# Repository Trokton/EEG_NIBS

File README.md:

# EEG_NIBS

🧠 Closed-Loop EEG & 4-Channel tACS/tDCS Neurostimulation System

Welcome to the documentation for a fully open-source, closed-loop EEG-integrated neurostimulation system, built entirely from scratch.

This repository contains the hardware designs, parts list, and firmware for a 4-channel tACS/tDCS stimulation system with real-time EEG integration, controlled via Python and Arduino Nano.

⸻

🧩 Project Overview

This system was developed to explore adaptive brain stimulation — modulating electrical currents based on real-time brain states, cognitive performance, or reinforcement learning algorithms.

Key Components:
	•	🧠 EEG Recording Module
	•	⚡ 4-Channel tDCS/tACS Stimulation Hardware
	•	🔁 Closed-Loop Python Control System
	•	🖥️ Arduino-based DAC current control
	•	🔐 Built-in Safety Features & Logging

The system is designed to serve researchers and developers interested in:
	•	Personalized neurostimulation
	•	Cognitive enhancement
	•	Reinforcement learning in neuroscience
	•	Brain-computer interfaces (BCIs)
	•	DIY neuroscience and open science hardware

⸻

🎯 Purpose

To provide a low-cost, flexible, and safe neurotechnology platform for:
	•	Closed-loop stimulation experiments
	•	Adaptive stimulation based on EEG/behavioral input
	•	Neuroscientific prototyping for brain state modulation
	•	Psychophysiological experiments

⸻

🛠️ Hardware Specifications

🔌 Stimulation Module (4-Channel tDCS/tACS)

Spec	Value/Feature
Channels	4 (individually addressable)
Max Current (per channel)	4 mA
Modulation Modes	tDCS, tACS (Sine, Square, Ramp, Custom)
Control Interface	Arduino Nano + DAC7311
Current Regulation	DAC-controlled + precision resistors
Voltage Reference	REF5050 or ADR5041 (5.0V)
Safety Features	Emergency analog cut-off, max current limit, resistance monitoring
Program Modes	5 fixed presets (2 x tDCS, 3 x tACS)
Control UI	1.3” OLED + 4 Buttons (Program, Start/Stop, ±Current)
Power Supply	Lab power (battery optional)

⸻

🧠 EEG Integration
	•	Interface for real-time EEG signal acquisition (designed for compatibility with OpenBCI or DIY amplifier)
	•	Real-time data streaming to Python
	•	Used to compute state, reward, and adaptation signals
	•	Clean switching logic to avoid interference during stimulation
	•	Log-based and adaptive session management

⸻

🧰 Bill of Materials (BoM)

(Full parts list available in parts_catalog.xlsx)

Example components:
	•	Arduino Nano (x4)
	•	DAC7311IDCKR (x2)
	•	TLC2252 Op-Amps (x4)
	•	REF5050 / ADR5041 Voltage Reference
	•	86.6Ω, 1.2kΩ, 2.2kΩ precision resistors
	•	1µF MLCC capacitors
	•	L78L05 voltage regulator
	•	SI8630BD Digital Isolator
	•	FMMT734/634 Darlington Transistors
	•	OLED 1.3” Display
	•	Tactile Buttons (x4)
	•	Toggle/Emergency Switch
	•	XL6009 Boost Converter

⸻

💻 Software / Firmware
	•	Arduino Sketches: arduino_code/
	•	Python Control Scripts (planned): python_control/
	•	EEG Integration & Analysis: eeg_pipeline/
	•	Safety & Log Scripts: logs/

⸻

🔄 Closed-Loop Flow
	1.	Cognitive Task → EEG + Task Performance Monitoring
	2.	Python Agent → Define State
	3.	RL Algorithm → Select Stimulation Protocol (Action)
	4.	Arduino Executes Program via DAC
	5.	EEG Feedback → Reward + Adaptation

⸻

📷 Visuals

PCB Layout, 3D Case Design, and Build Photos are included in assets/.

⸻

⚠️ Safety Notes
	•	Always monitor electrode resistance.
	•	Do not exceed 4 mA/channel.
	•	Use ramp-up/ramp-down transitions.
	•	Test with resistive dummy loads before skin contact.

⸻

👤 Author

Developed by Michael Roehrig, psychologist & AI enthusiast, diving into DIY neurotech to build accessible and intelligent brain interfaces.

Inspired by the incredible work of Prof. Roi Cohen Kadosh and open science communities.

⸻

📩 Contact & Collaboration

Interested in collaboration, replication, or feedback? Let’s connect via LinkedIn or GitHub issues!

⸻

📜 License

Open-source for research and educational use. Use responsibly. Not intended for clinical/medical use.

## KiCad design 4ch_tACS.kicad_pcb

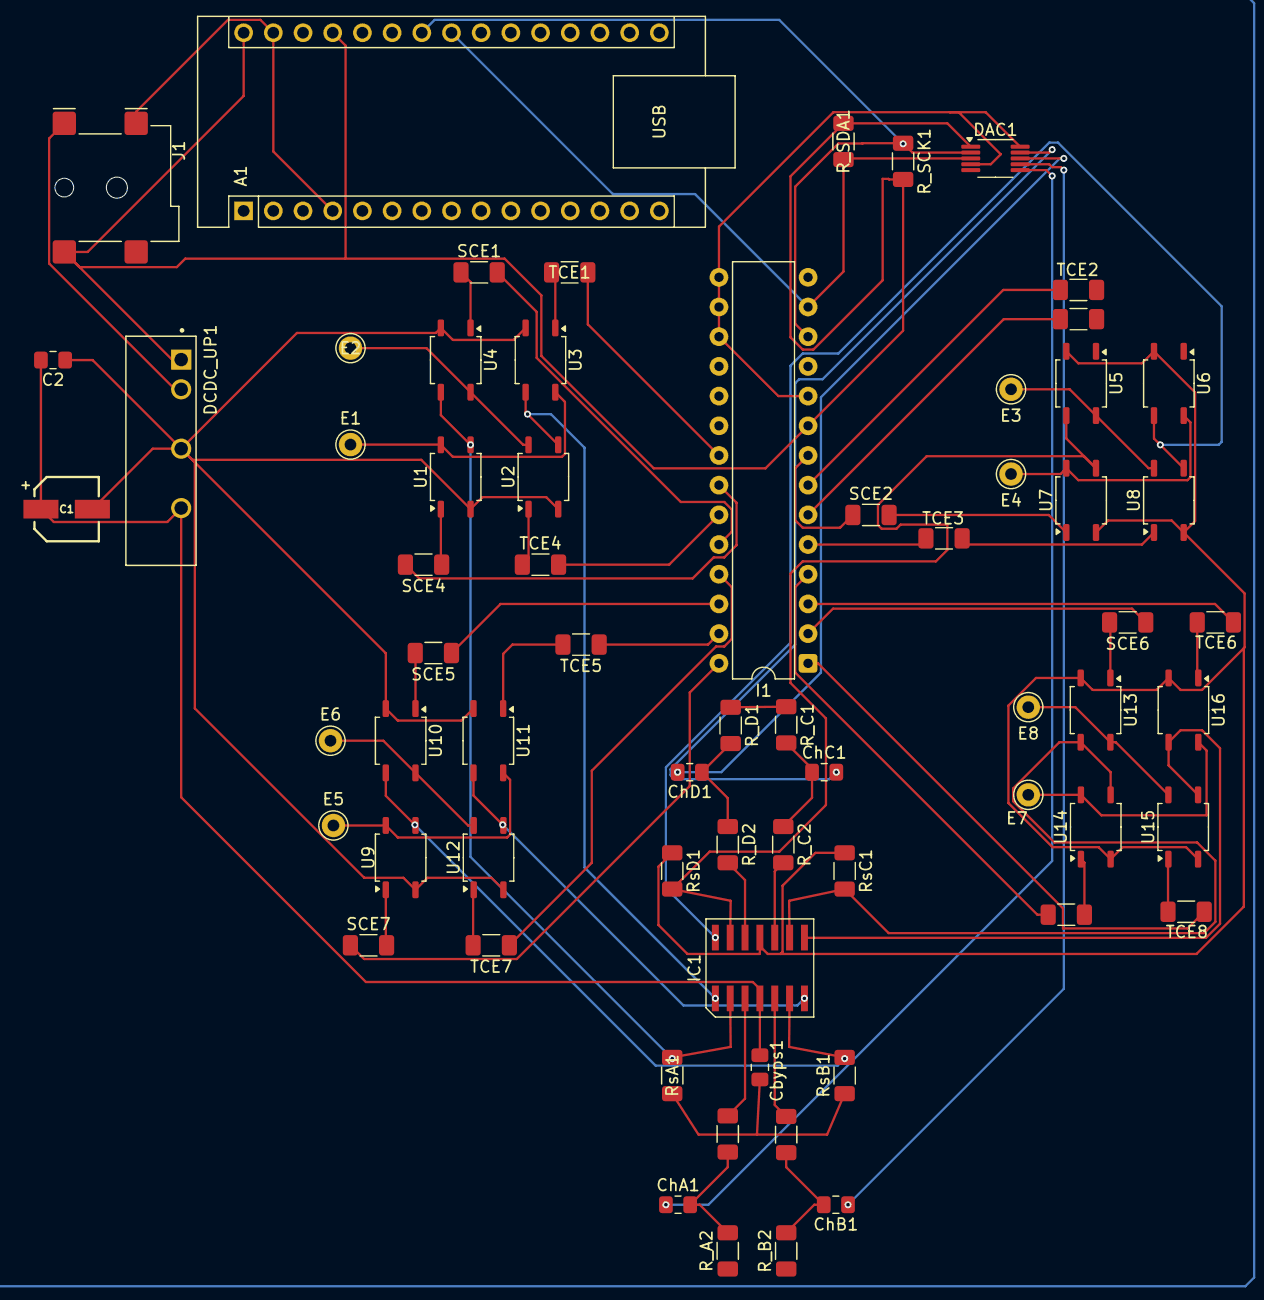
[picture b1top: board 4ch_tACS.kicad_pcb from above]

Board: 2 copper layers, 67 parts (0 on the bottom side), 66 nets.

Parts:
A1: Arduino_Nano_v3.x; Arduino_Nano
C1: 10uF; WCAP-AS5H_5X5.5_DXL_
C2: 0.1 uF; C_0805_2012Metric_Pad1.18x1.45mm_HandSolder
Cbyps1: 0.1 uF; C_0805_2012Metric_Pad1.18x1.45mm_HandSolder
ChA1: 10 uF; C_0805_2012Metric_Pad1.18x1.45mm_HandSolder
ChB1: 10 uF; C_0805_2012Metric_Pad1.18x1.45mm_HandSolder
ChC1: 10 uF; C_0805_2012Metric_Pad1.18x1.45mm_HandSolder
ChD1: 10 uF; C_0805_2012Metric_Pad1.18x1.45mm_HandSolder
DAC1: MCP4728; MSOP-10_3x3mm_P0.5mm
DCDC_UP1: RE-0524S; CONV_RE-0524S
E1: Stim1; Pin_D1.0mm_L10.0mm
E2: Stim2; Pin_D1.0mm_L10.0mm
E3: Stim7; Pin_D1.0mm_L10.0mm
E4: Stim8; Pin_D1.0mm_L10.0mm
E5: Stim4; Pin_D1.0mm_L10.0mm
E6: Stim3; Pin_D1.0mm_L10.0mm
E7: Stim6; Pin_D1.0mm_L10.0mm
E8: Stim5; Pin_D1.0mm_L10.0mm
I1: MCP23017_SP; DIP-28_W7.62mm
IC1: OPA1664AIDR; SOIC127P600X175-14N
J1: Barrel_Jack; BarrelJack_Wuerth_694106106102_2.0x5.5mm
R_A1: 1k; R_1206_3216Metric_Pad1.30x1.75mm_HandSolder
R_A2: 100k; R_1206_3216Metric_Pad1.30x1.75mm_HandSolder
R_B1: 1k; R_1206_3216Metric_Pad1.30x1.75mm_HandSolder
R_B2: 100k; R_1206_3216Metric_Pad1.30x1.75mm_HandSolder
R_C1: 100k; R_1206_3216Metric_Pad1.30x1.75mm_HandSolder
R_C2: 1k; R_1206_3216Metric_Pad1.30x1.75mm_HandSolder
R_D1: 100k; R_1206_3216Metric_Pad1.30x1.75mm_HandSolder
R_D2: 1k; R_1206_3216Metric_Pad1.30x1.75mm_HandSolder
R_SCK1: 4.7k; R_1206_3216Metric_Pad1.30x1.75mm_HandSolder
R_SDA1: 4.7k; R_1206_3216Metric_Pad1.30x1.75mm_HandSolder
RsA1: 1.2k; R_1206_3216Metric_Pad1.30x1.75mm_HandSolder
RsB1: 1.2k; R_1206_3216Metric_Pad1.30x1.75mm_HandSolder
RsC1: 1.2k; R_1206_3216Metric_Pad1.30x1.75mm_HandSolder
RsD1: 1.2k; R_1206_3216Metric_Pad1.30x1.75mm_HandSolder
SCE1, SCE2, SCE3, SCE4, SCE5, SCE6, SCE7, SCE8: 470; R_1206_3216Metric_Pad1.30x1.75mm_HandSolder
TCE1, TCE2, TCE3, TCE4, TCE5, TCE6, TCE7, TCE8: 470; R_1206_3216Metric_Pad1.30x1.75mm_HandSolder
U1: SE1; SOP-4_3.8x4.1mm_P2.54mm
U2: TE2; SOP-4_3.8x4.1mm_P2.54mm
U3: TE1; SOP-4_3.8x4.1mm_P2.54mm
U4: SE2; SOP-4_3.8x4.1mm_P2.54mm
U5: SE7; SOP-4_3.8x4.1mm_P2.54mm
U6: TE8; SOP-4_3.8x4.1mm_P2.54mm
U7: SE8; SOP-4_3.8x4.1mm_P2.54mm
U8: TE7; SOP-4_3.8x4.1mm_P2.54mm
U9: SE4; SOP-4_3.8x4.1mm_P2.54mm
U10: SE3; SOP-4_3.8x4.1mm_P2.54mm
U11: TE4; SOP-4_3.8x4.1mm_P2.54mm
U12: TE3; SOP-4_3.8x4.1mm_P2.54mm
U13: SE5; SOP-4_3.8x4.1mm_P2.54mm
U14: SE6; SOP-4_3.8x4.1mm_P2.54mm
U15: TE5; SOP-4_3.8x4.1mm_P2.54mm
U16: TE6; SOP-4_3.8x4.1mm_P2.54mm

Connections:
/24V_GND: C1.2, C2.1, Cbyps1.2, DCDC_UP1.4 (-VOUT), IC1.11 (V-), RsA1.1, RsB1.1, RsC1.1, RsD1.1, U1.2, U2.2, U3.2, U4.2, U5.2, U6.2, U7.2, U8.2, U9.2, U10.2, U11.2, U12.2, U13.2, U14.2, U15.2, U16.2
/+5V: A1.27 (+5V), A1.30 (VIN), DAC1.1 (VDD), DCDC_UP1.1 (+VIN), I1.9 (VDD), J1.2, R_SCK1.2, R_SDA1.1
/+24V: C1.1, C2.2, Cbyps1.1, DCDC_UP1.6 (+VOUT), IC1.4 (V+)
/ChA_net: IC1.3 (+INA), R_A1.2
/ChB_net: IC1.5 (+INB), R_B1.2
/ChC_net: IC1.10 (+INC), R_C2.2
/ChD_net: IC1.12 (+IND), R_D2.2
/Sl_A: IC1.2 (-INA), RsA1.2, U1.3, U4.3
/Sl_B: IC1.6 (-INB), RsB1.2, U9.3, U10.3
/Sl_C: IC1.9 (-INC), RsC1.2, U13.3, U14.3
/Sl_D: IC1.13 (-IND), RsD1.2, U5.3, U7.3
unnamed: A1.23 (A4), DAC1.3 (SDA), I1.13 (SDA), R_SDA1.2
unnamed: A1.24 (A5), DAC1.2 (SCL), I1.12 (SCK), R_SCK1.1
unnamed: ChA1.2, R_A1.1, R_A2.2
unnamed: ChB1.2, R_B1.1, R_B2.2
unnamed: ChC1.1, R_C1.2, R_C2.1
unnamed: ChD1.1, R_D1.2, R_D2.1
unnamed: ChA1.1, DAC1.6 (VOUTA)
unnamed: ChB1.1, DAC1.7 (VOUTB)
unnamed: ChD1.2, DAC1.8 (VOUTC)
unnamed: ChC1.2, DAC1.9 (VOUTD)
unnamed: A1.4 (GND), A1.29 (GND), DAC1.4 (~LDAC), DAC1.10 (VSS), DCDC_UP1.2 (-VIN), I1.10 (VSS), I1.15 (A0), I1.16 (A1), I1.17 (A2), J1.1, R_A2.1, R_B2.1, R_C1.1, R_D1.1
unnamed: E1.1, U1.4, U3.4
unnamed: E2.E2, U2.4, U4.4
unnamed: E6.1, U10.4, U12.4
unnamed: E5.1, U9.4, U11.4
unnamed: E8.1, U13.4, U15.4
unnamed: E7.1, U14.4, U16.4
unnamed: E3.1, U5.4, U8.4
unnamed: E4.1, U6.4, U7.4
unnamed: I1.21 (GPA0), TCE1.2
unnamed: I1.22 (GPA1), SCE4.2
unnamed: I1.23 (GPA2), TCE4.2
unnamed: I1.24 (GPA3), SCE1.2
unnamed: I1.25 (GPA4), TCE7.1
unnamed: I1.26 (GPA5), SCE5.1
unnamed: I1.27 (GPA6), TCE5.1
unnamed: I1.28 (GPA7), SCE7.1
unnamed: I1.1 (GPB0), TCE8.1
unnamed: I1.2 (GPB1), SCE6.1
unnamed: I1.3 (GPB2), TCE6.1
unnamed: I1.4 (GPB3), SCE8.1
unnamed: I1.5 (GPB4), TCE3.1
unnamed: I1.6 (GPB5), SCE3.1
unnamed: I1.7 (GPB6), TCE2.1
unnamed: I1.8 (GPB7), SCE2.1
unnamed: IC1.1 (OUTA), U2.3, U3.3
unnamed: IC1.7 (OUTB), U11.3, U12.3
unnamed: IC1.8 (OUTC), U15.3, U16.3
unnamed: IC1.14 (OUTD), U6.3, U8.3
unnamed: SCE6.2, U13.1
unnamed: SCE8.2, U14.1
unnamed: SCE3.2, U5.1
unnamed: SCE2.2, U7.1
unnamed: SCE4.1, U1.1
unnamed: SCE1.1, U4.1
unnamed: SCE5.2, U10.1
unnamed: SCE7.2, U9.1
unnamed: TCE8.2, U15.1
unnamed: TCE6.2, U16.1
unnamed: TCE3.2, U8.1
unnamed: TCE2.2, U6.1
unnamed: TCE1.1, U3.1
unnamed: TCE4.1, U2.1
unnamed: TCE7.2, U12.1
unnamed: TCE5.2, U11.1

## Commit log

2025-03-04 First setup and playaround
2025-03-04 Data template
2025-03-04 Threading mode implemented
2025-03-05 Restructured class EEGRecorder
2025-03-31 Hardware layout of the NIBS circuit
    4-Channel tACS/tDCS device with arbitrary assignment of each electrode as channels anode or cathode
